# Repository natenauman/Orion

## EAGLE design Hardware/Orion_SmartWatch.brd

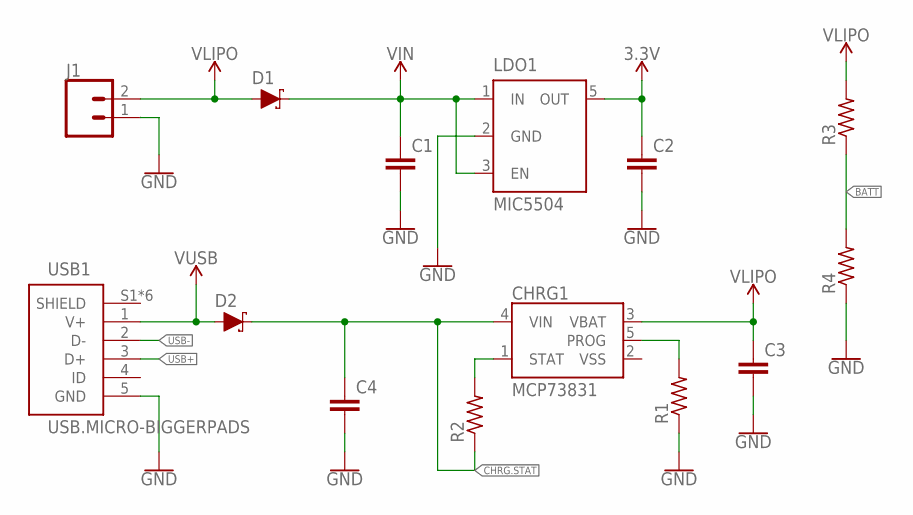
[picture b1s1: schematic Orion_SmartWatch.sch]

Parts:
C1, C2, C3, C4: CAPACITOR0603; C0603
CHRG1: MCP73831; SOT23-5
D1, D2: SCHOTTKY-USC; USC
J1: CONN_02; 1X02
LDO1: MIC5504; SOT23-5
R1, R2, R3, R4: RESISTOR0603; R0603
USB1: USB.MICRO-BIGGERPADS; USB-MICRO-01.BIGGERPADS

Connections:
3.3V: C2.1, LDO1.5 (OUT)
BATT: R3.1, R4.2
CHRG.STAT: C4.1, CHRG1.4 (VIN), D2.- (C), R2.1
GND: C1.2, C2.2, C3.2, C4.2, J1.1, LDO1.2 (GND), R1.1, R4.1, USB1.5 (GND)
unnamed: CHRG1.1 (STAT), R2.2
unnamed: CHRG1.5 (PROG), R1.2
USB+: USB1.3 (D+)
USB-: USB1.2 (D-)
VIN: C1.1, D1.- (C), LDO1.1 (IN), LDO1.3 (EN)
VLIPO: C3.1, CHRG1.3 (VBAT), D1.+ (A), J1.2, R3.2
VSS: CHRG1.2 (VSS)
V_USB: D2.+ (A), USB1.1 (V+)

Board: 2 copper layers, 14 parts (0 on the bottom side), 9 nets, no tracks yet.

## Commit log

2020-02-02 Adding Firmware
2020-02-02 Adding Hardware
